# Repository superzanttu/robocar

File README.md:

# robocar
Project to test and learn how to create autonomous robot.

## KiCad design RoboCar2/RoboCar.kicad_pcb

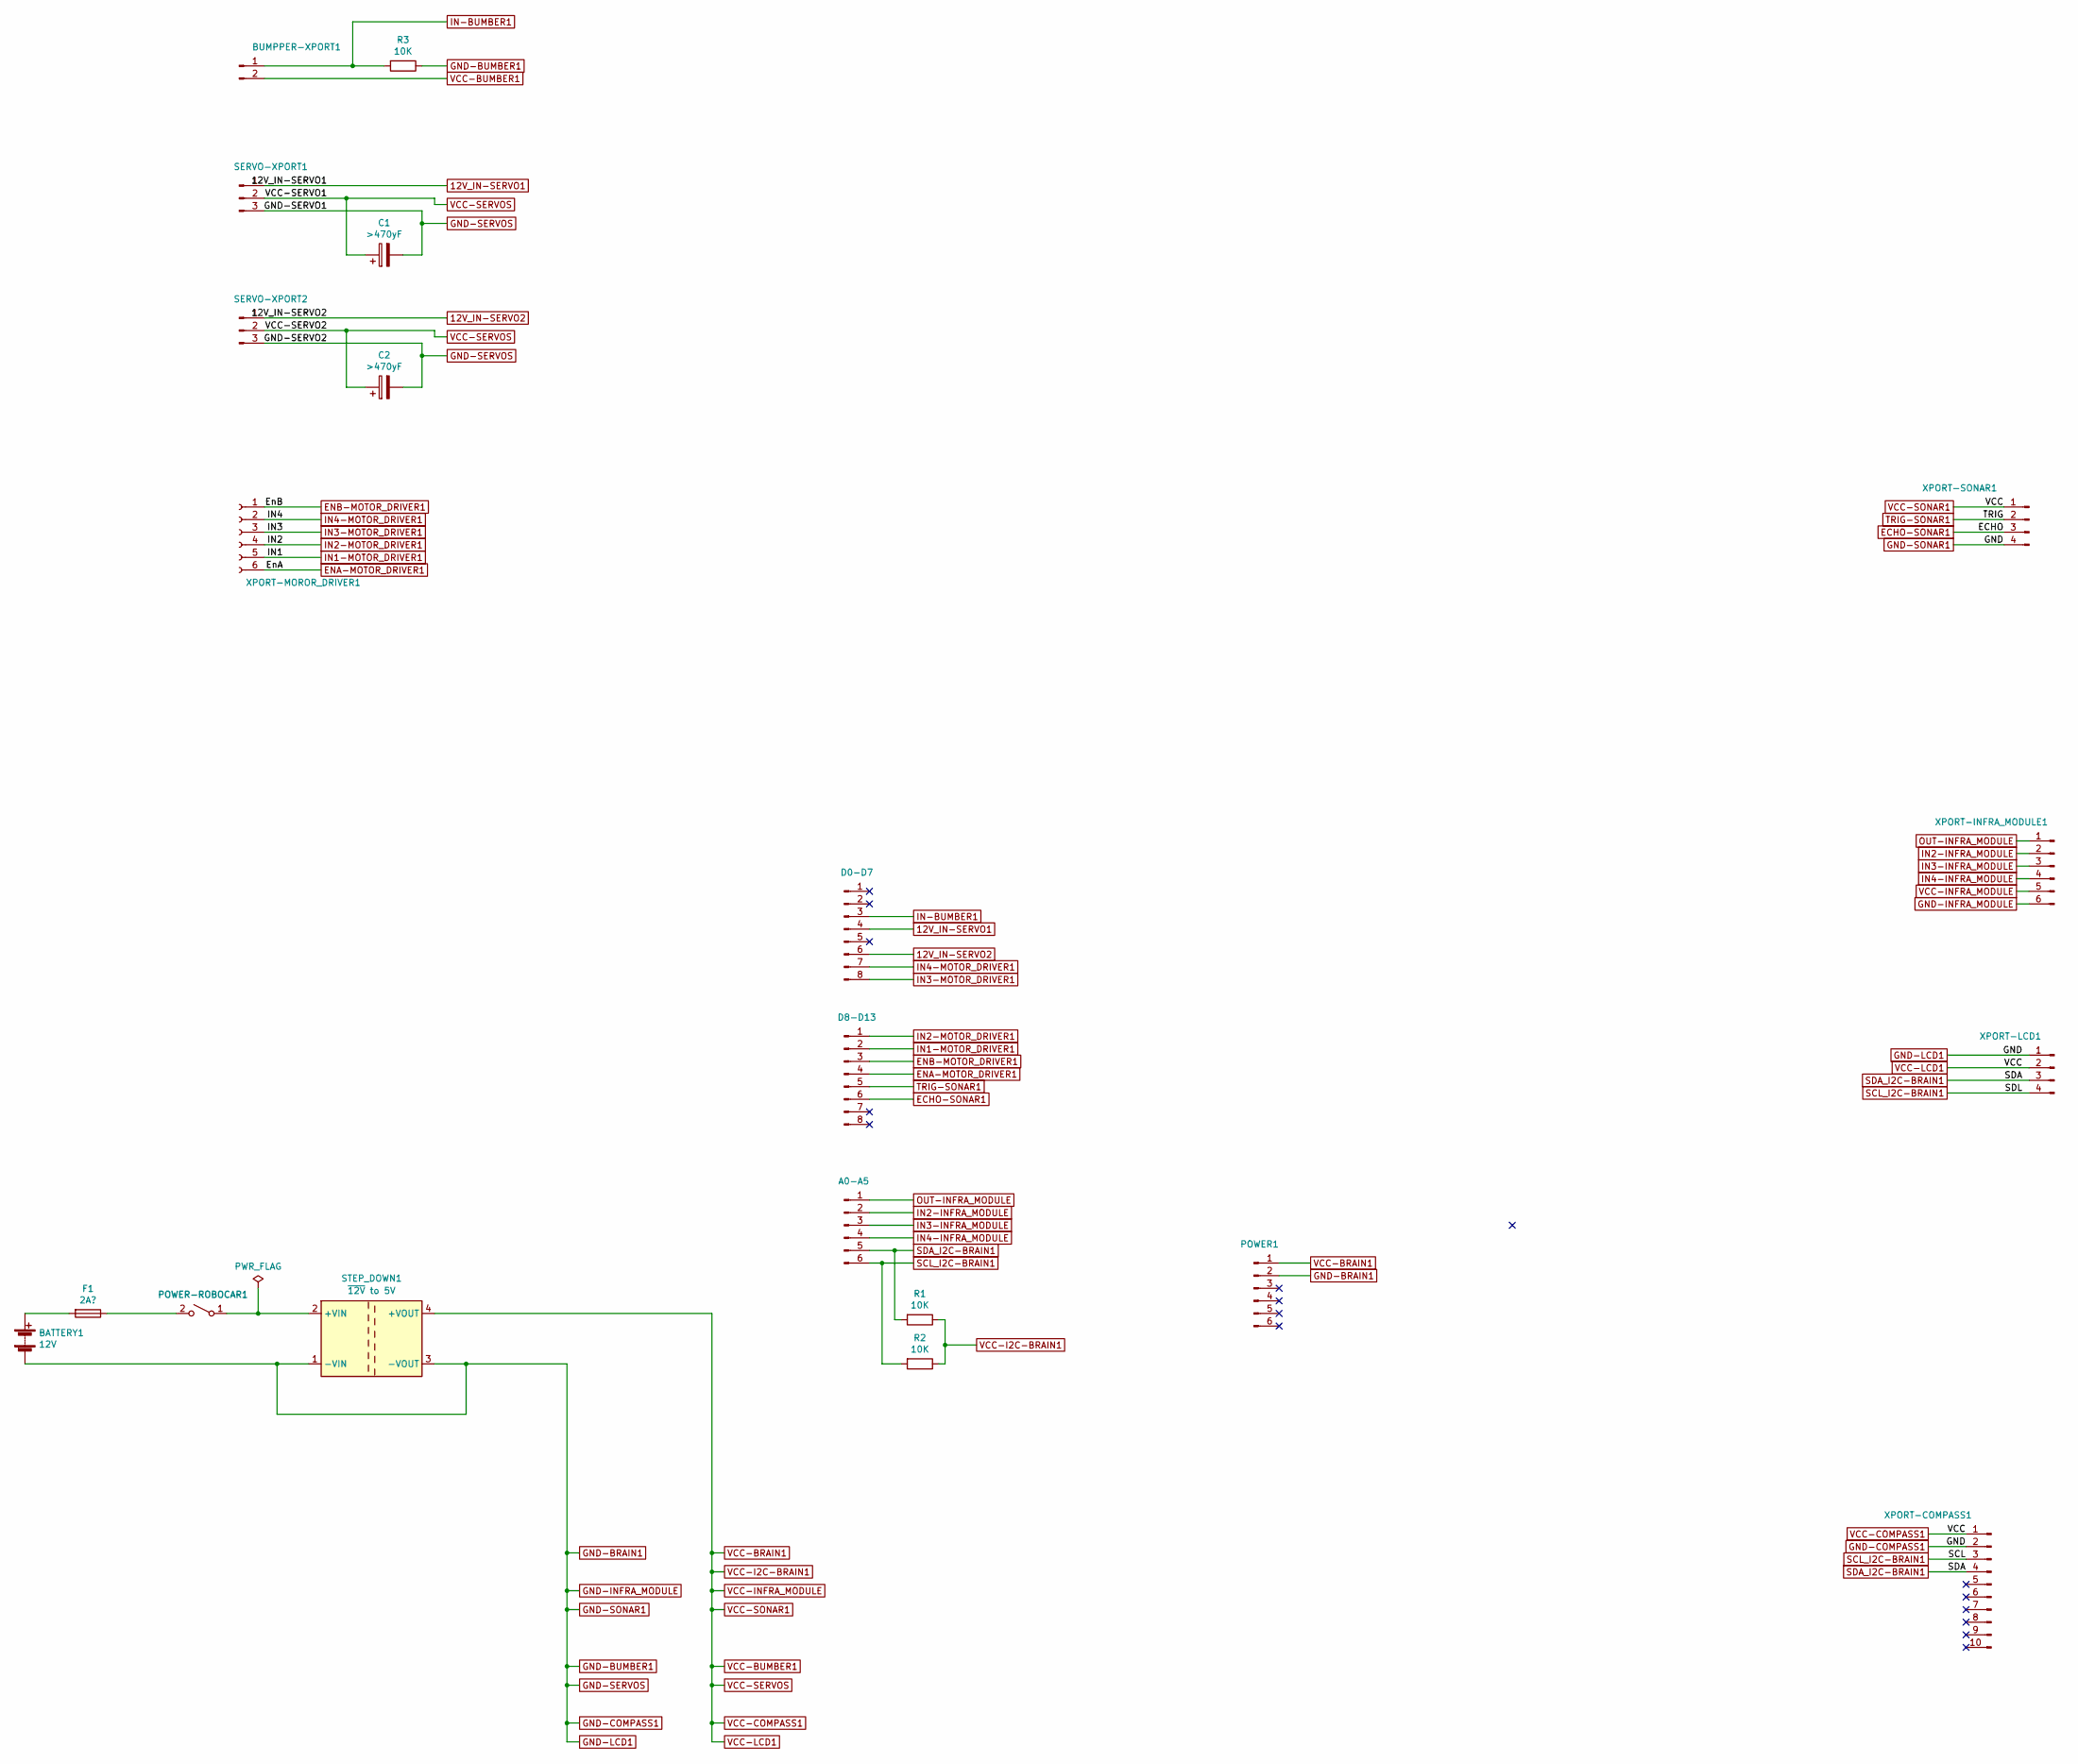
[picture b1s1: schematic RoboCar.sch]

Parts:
A0-A5: Conn_01x06_Male; PinHeader_1x06_P1.27mm_Vertical
BATTERY1: 12V; BatteryHolder_Keystone_3034_1x20mm
BUMPPER-XPORT1: Conn_01x02_Male; PinHeader_1x02_P1.27mm_Vertical
C1, C2: >470yF; CP_Radial_D8.0mm_P5.00mm
D0-D7, D8-D13: Conn_01x08_Male; PinHeader_1x08_P1.27mm_Vertical
F1: 2A?; Fuseholder_Blade_ATO_Littelfuse_Pudenz_2_Pin
POWER1: Conn_01x06_Male; PinHeader_1x06_P1.27mm_Vertical
POWER-ROBOCAR1: SW_SPST; SW_DIP_SPSTx01_Slide_9.78x4.72mm_W7.62mm_P2.54mm
R1, R2, R3: 10K; R_Axial_DIN0204_L3.6mm_D1.6mm_P7.62mm_Horizontal
SERVO-XPORT1, SERVO-XPORT2: Conn_01x03_Male; PinHeader_1x03_P1.27mm_Vertical
STEP_DOWN1: ~12V to 5V; Converter_DCDC_muRata_CRE1xxxxxxSC_THT
XPORT-COMPASS1: Conn_01x10_Male; PinHeader_1x10_P1.27mm_Vertical
XPORT-INFRA_MODULE1: Conn_01x06_Male; PinHeader_1x06_P1.27mm_Vertical
XPORT-LCD1: Conn_01x04_Male; PinHeader_1x04_P1.27mm_Vertical
XPORT-MOROR_DRIVER1: Conn_01x06_Female; PinSocket_1x06_P1.27mm_Vertical
XPORT-SONAR1: Conn_01x04_Male; PinHeader_1x04_P1.27mm_Vertical

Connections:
12V_IN-SERVO1: D0-D7.4, SERVO-XPORT1.1
12V_IN-SERVO2: D0-D7.6, SERVO-XPORT2.1
ECHO-SONAR1: D8-D13.6, XPORT-SONAR1.3
ENA-MOTOR_DRIVER1: D8-D13.4, XPORT-MOROR_DRIVER1.6
ENB-MOTOR_DRIVER1: D8-D13.3, XPORT-MOROR_DRIVER1.1
GND-BRAIN1: BATTERY1.2 (-), C1.2, C2.2, POWER1.2, R3.1, SERVO-XPORT1.3, SERVO-XPORT2.3, STEP_DOWN1.1 (-VIN), STEP_DOWN1.3 (-VOUT), XPORT-COMPASS1.2, XPORT-INFRA_MODULE1.6, XPORT-LCD1.1, XPORT-SONAR1.4
IN1-MOTOR_DRIVER1: D8-D13.2, XPORT-MOROR_DRIVER1.5
IN2-INFRA_MODULE: A0-A5.2, XPORT-INFRA_MODULE1.2
IN2-MOTOR_DRIVER1: D8-D13.1, XPORT-MOROR_DRIVER1.4
IN3-INFRA_MODULE: A0-A5.3, XPORT-INFRA_MODULE1.3
IN3-MOTOR_DRIVER1: D0-D7.8, XPORT-MOROR_DRIVER1.3
IN4-INFRA_MODULE: A0-A5.4, XPORT-INFRA_MODULE1.4
IN4-MOTOR_DRIVER1: D0-D7.7, XPORT-MOROR_DRIVER1.2
IN-BUMBER1: BUMPPER-XPORT1.1, D0-D7.3, R3.2
unnamed: BATTERY1.1 (+), F1.2
unnamed: F1.1, POWER-ROBOCAR1.2 (B)
unnamed: POWER-ROBOCAR1.1 (A), STEP_DOWN1.2 (+VIN)
OUT-INFRA_MODULE: A0-A5.1, XPORT-INFRA_MODULE1.1
SCL_I2C-BRAIN1: A0-A5.6, R2.2, XPORT-COMPASS1.3, XPORT-LCD1.4
SDA_I2C-BRAIN1: A0-A5.5, R1.2, XPORT-COMPASS1.4, XPORT-LCD1.3
TRIG-SONAR1: D8-D13.5, XPORT-SONAR1.2
VCC-BRAIN1: BUMPPER-XPORT1.2, C1.1, C2.1, POWER1.1, R1.1, R2.1, SERVO-XPORT1.2, SERVO-XPORT2.2, STEP_DOWN1.4 (+VOUT), XPORT-COMPASS1.1, XPORT-INFRA_MODULE1.5, XPORT-LCD1.2, XPORT-SONAR1.1

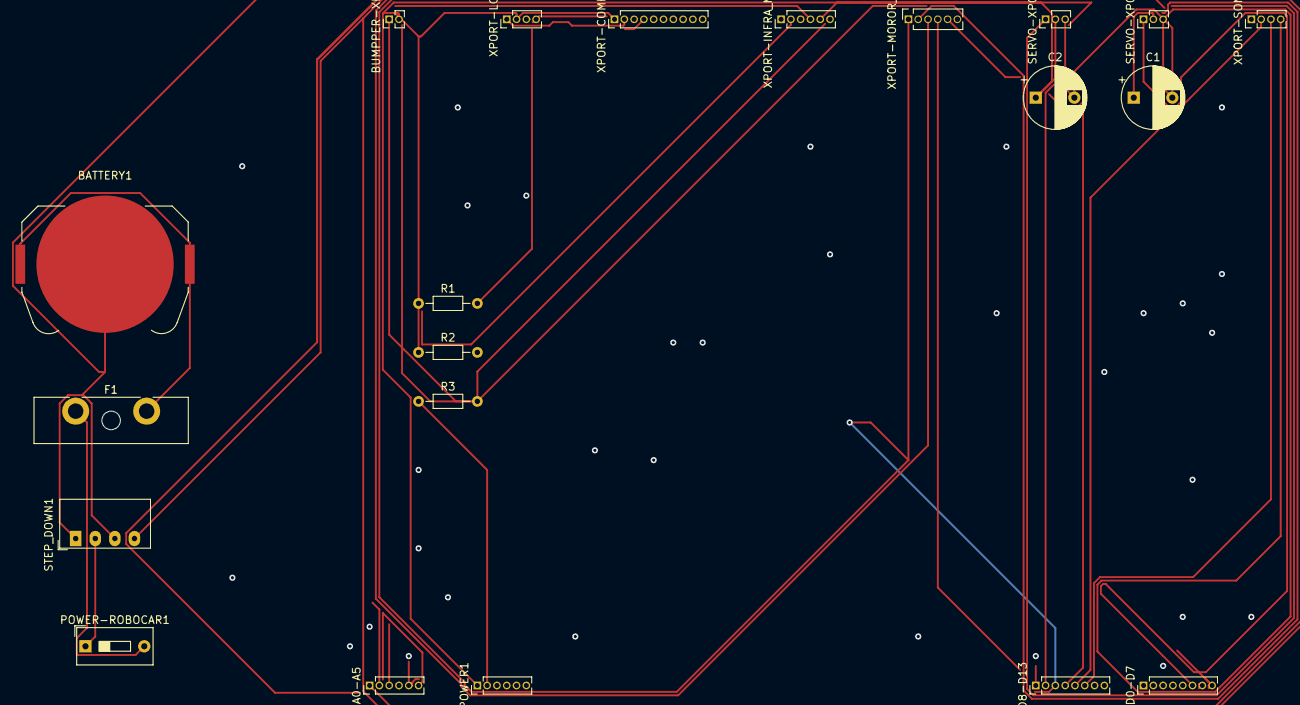
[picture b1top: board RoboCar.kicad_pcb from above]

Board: 2 copper layers, 21 parts (0 on the bottom side), 22 nets.
